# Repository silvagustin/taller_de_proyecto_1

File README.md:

# Proyecto: Control para una matriz de LEDs

### Palabras clave:
- EDU CIAA-NXP, CIAA, poncho, shield, matriz de leds 8x8, LCD 1602,LCD 16x02, teclado matricial.

### Interfaces:
- LCD 16x02
- Teclado Matricial 4 filas 3 columnas

### Grupo 5, integrantes:
- Buján Ariel,   157/0
- Delgado David, 139/8
- Silva Agustín, 63/5

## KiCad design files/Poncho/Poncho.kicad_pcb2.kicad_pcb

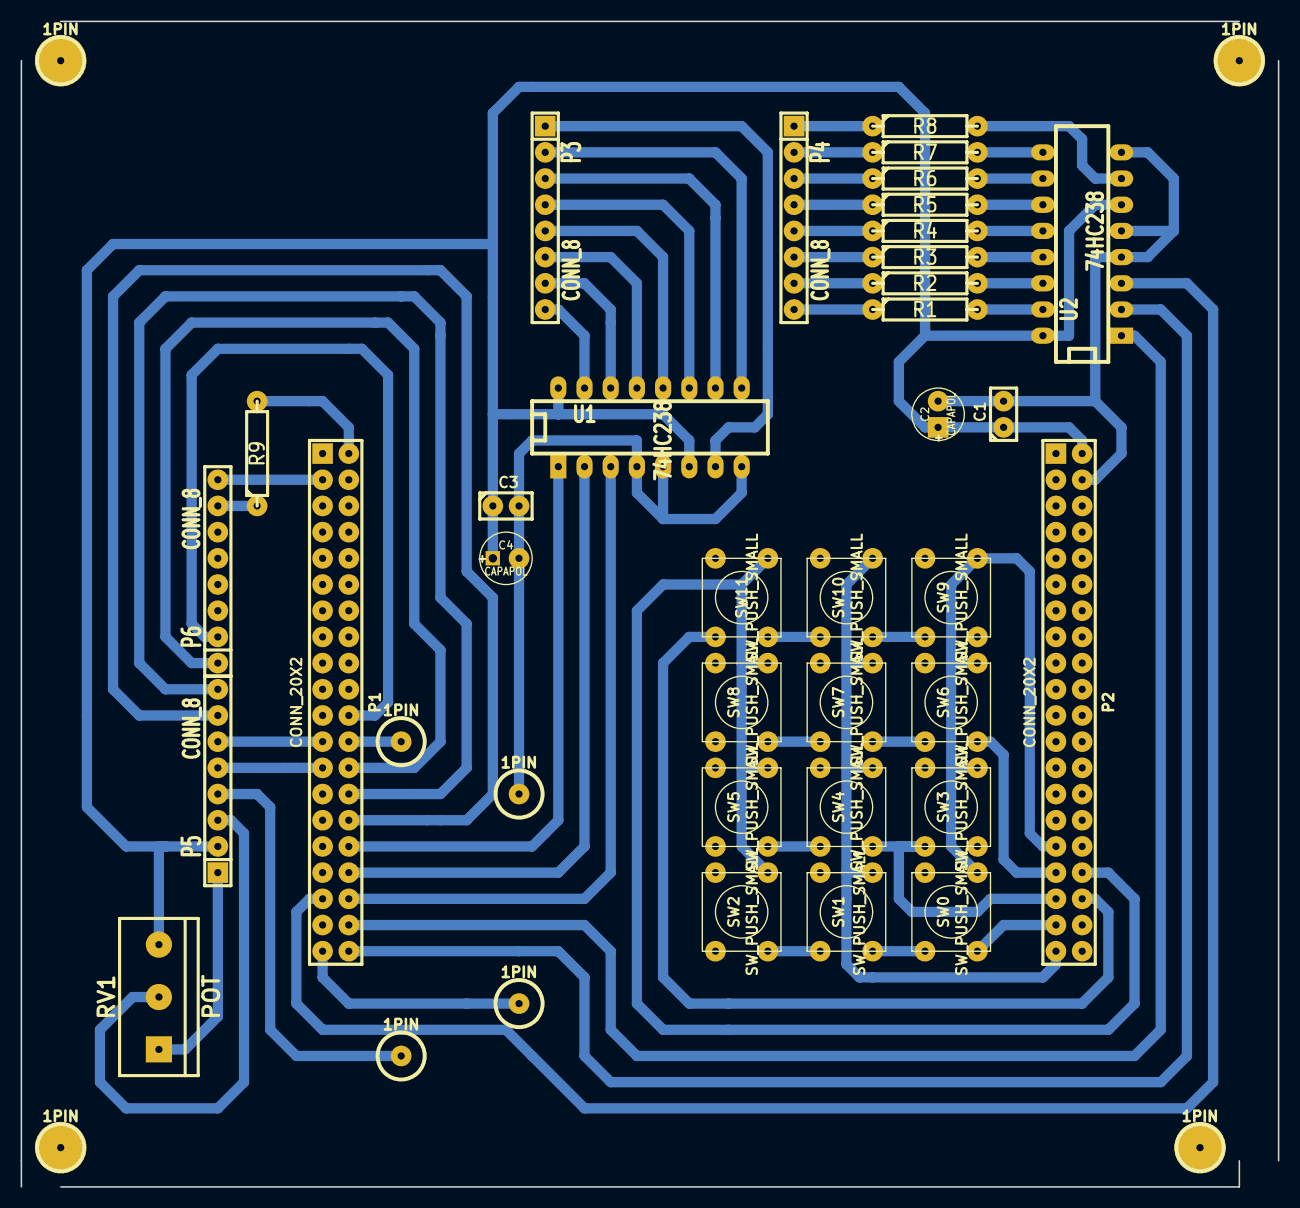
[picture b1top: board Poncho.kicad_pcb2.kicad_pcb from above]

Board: 2 copper layers, 121.9 x 113.0 mm, 42 parts (0 on the bottom side), 50 nets.

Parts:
1PIN, 1PIN#2, 1PIN#3, 1PIN#4, 1PIN#5, 1PIN#6, 1PIN#7, 1PIN#8: P***; 1pin
C1, C3: C; C1
C2, C4: CAPAPOL; C1V5
P1, P2: CONN_20X2; PIN_ARRAY_20X2
P3, P4, P5, P6: CONN_8; SIL-8
R1, R2, R3, R4, R5, R6, R7, R8, R9: R; R4
RV1: POT; bornier3
SW0, SW1, SW2, SW3, SW4, SW5, SW6, SW7, SW8, SW9, SW10, SW11: SW_PUSH_SMALL; SW_PUSH_SMALL_I
U1, U2: 74HC238; DIP-16__300_ELL

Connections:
GND: 1PIN.1, 1PIN#2.1, 1PIN#3.1, 1PIN#4.1, C1.2, C2.2, C3.2, C4.2, P1.39, P2.4, U1.4, U1.5, U1.8, U2.4, U2.5, U2.8
unnamed: P6.7, R9.1
unnamed: P3.6, U1.13
unnamed: P3.5, U1.12
unnamed: P3.4, U1.11
unnamed: P3.3, U1.10
unnamed: P1.23, P5.6
unnamed: P3.1, U1.7
unnamed: P1.28, P5.8
unnamed: P1.34, U1.2
unnamed: P1.32, U1.1
unnamed: P1.36, U1.3
unnamed: P1.38, U2.1
unnamed: P1.35, U2.3
unnamed: P1.24, P5.4
unnamed: P1.22, P6.2
unnamed: P1.26, P6.1
unnamed: P1.30, P5.7
unnamed: P5.3, RV1.2
unnamed: P4.7, R2.1
unnamed: P3.2, U1.9
unnamed: P1.40, U2.2
unnamed: P1.3, P6.8
unnamed: P1.2, R9.2
unnamed: R7.2, U2.9
unnamed: P4.8, R1.1
unnamed: P4.6, R3.1
unnamed: P4.5, R4.1
unnamed: P4.4, R5.1
unnamed: P4.3, R6.1
unnamed: P4.2, R7.1
unnamed: P4.1, R8.1
unnamed: R8.2, U2.7
unnamed: R6.2, U2.10
unnamed: R5.2, U2.11
unnamed: R4.2, U2.12
unnamed: R3.2, U2.13
unnamed: R2.2, U2.14
unnamed: R1.2, U2.15
unnamed: P3.7, U1.14
unnamed: P3.8, U1.15
unnamed: P1.25, P5.1, P5.5, RV1.1
unnamed: P2.35, SW3.2, SW4.2, SW5.2
unnamed: P2.37, SW0.2, SW1.2, SW2.2
unnamed: P2.39, SW1.1, SW4.1, SW7.1, SW10.1
unnamed: P2.33, SW6.2, SW7.2, SW8.2
unnamed: P2.34, SW2.1, SW5.1, SW8.1, SW11.1
unnamed: P2.31, SW0.1, SW3.1, SW6.1, SW9.1
unnamed: P2.36, SW9.2, SW10.2, SW11.2
VCC: C1.1, C2.1, C3.1, C4.1, P2.2, P5.2, RV1.3, U1.6, U1.16, U2.6, U2.16

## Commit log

2016-02-10 Firmware
2016-02-10 Actualizacion
2016-02-10 modificacion del informe
2016-02-10 cambiado nombre en makefile.mine
2016-02-11 Actualización Informe 11/02/2016
2016-02-11 Agregadas imagenes del poncho para la documentación.
2016-02-12 actualización de diapositivas
2016-02-13 Actualización del Informe Técnico
2016-02-20 Actualización de Esquematicos
